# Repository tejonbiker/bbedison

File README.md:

# bbedison

The concept of the Intel Edison is great, but require skills (some skills are very advanced) to start working with this tiny invention.

The concept of  [Sparkfun Blocks](https://www.sparkfun.com/search/results?term=sparkfun+blocks) is great, but lack the access to all the pins of the Edison (else you will require several blocks).

The Arduino board is a great way to start with Intel Edison, but is to big and breaks the esscence of the edison, besides that, this board don't have access to all the pins of the Edison.

So, is necesary to build a very expensive PCB (with very small traces and very [small connector](http://www.adafruit.com/product/2227)) to do an advanced prototype of the Intel Edison? 

The response is: not, here is where the [Minibreakout](https://www.sparkfun.com/products/13025) of the Intel Edison enters to the rescue, but not alone.

The mini breakout is not [breadboard](https://cdn.sparkfun.com//assets/parts/1/0/0/1/1/13025-03.jpg) friendly, but have others adavantages:

      -Lipo management (charge and regulators)
      -Serial and OTG connections
      -Power Up sequence management

BBedison is a series of PCBs that allows you (in conjunction with Edison minibreakout ) prototype in a more friendly way.

The best of all:

      -It's cheap: BBEdison base cost 5 USD (Yes 5 USD and you are ready to plug in in your breadboard)
      -It's very easy to do it in your home

Eager to start experimenting? check it out the  BBEdison_base.

Links of interest:
Instructable of BBEdison_base:  http://www.instructables.com/id/Plug-your-Intel-Edison-in-a-breadboard/
Hackaday post:  http://hackaday.com/2015/04/01/a-stack-of-boards-for-an-edison-breadboard-adapter/

Authors:

**Federico Ramos**

tejonbiker@gmail.com

[@tejonbiker](https://twitter.com/tejonBiker)

about me ([spanish](https://tejonbiker.wordpress.com/acerca-de-mi/))

**Xhabas Jimenez**

[@Sabasacustico](https://twitter.com/Sabasacustico)

The Inventors House [Hackerspace](http://blog.theinventorhouse.org/)

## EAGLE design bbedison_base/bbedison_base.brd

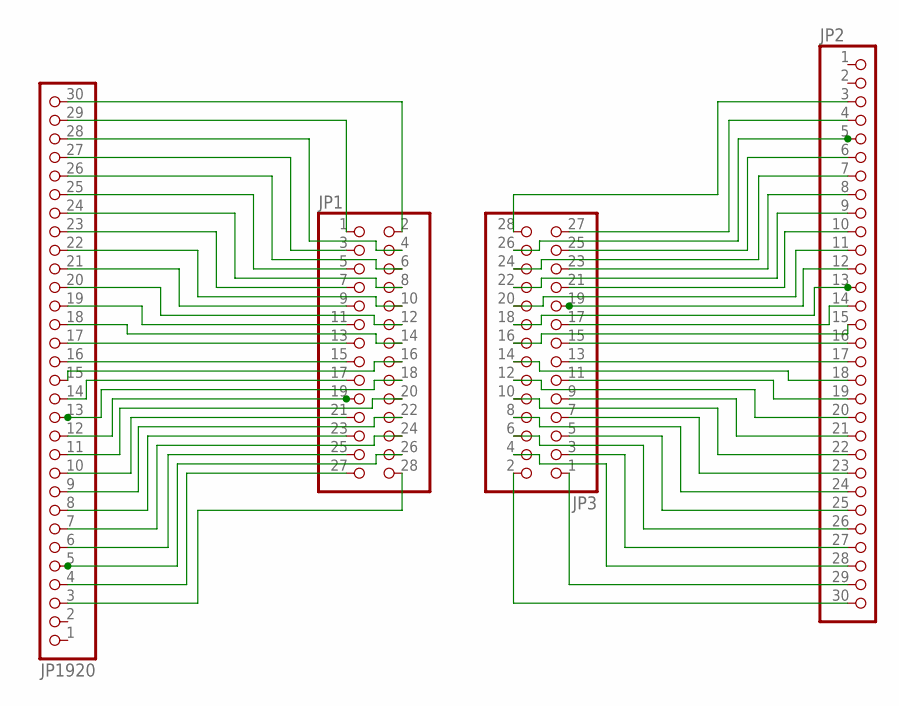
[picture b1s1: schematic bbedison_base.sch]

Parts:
JP1, JP3: PINHD-2X14; 2X14
JP2, JP1920: PINHD-1X30; 1X30

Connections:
unnamed: JP1.2, JP1920.30
unnamed: JP1.1, JP1920.29
unnamed: JP1.4, JP1920.28
unnamed: JP1.3, JP1920.27
unnamed: JP1.6, JP1920.26
unnamed: JP1.5, JP1920.25
unnamed: JP1.8, JP1920.24
unnamed: JP1.7, JP1920.23
unnamed: JP1.10, JP1920.22
unnamed: JP1.9, JP1920.21
unnamed: JP1.12, JP1920.20
unnamed: JP1.11, JP1920.19
unnamed: JP1.16, JP1920.15
unnamed: JP1.14, JP1920.18
unnamed: JP1.13, JP1920.17
unnamed: JP1.15, JP1920.16
unnamed: JP1.17, JP1920.14
unnamed: JP1.18, JP1920.13
unnamed: JP1.19, JP1920.12
unnamed: JP1.20, JP1920.11
unnamed: JP1.21, JP1920.10
unnamed: JP1.22, JP1920.9
unnamed: JP1.23, JP1920.8
unnamed: JP1.24, JP1920.7
unnamed: JP1.25, JP1920.6
unnamed: JP1.26, JP1920.5
unnamed: JP1.27, JP1920.4
unnamed: JP1.28, JP1920.3
unnamed: JP2.30, JP3.2
unnamed: JP2.29, JP3.1
unnamed: JP2.28, JP3.4
unnamed: JP2.27, JP3.3
unnamed: JP2.26, JP3.6
unnamed: JP2.25, JP3.5
unnamed: JP2.24, JP3.8
unnamed: JP2.23, JP3.7
unnamed: JP2.22, JP3.10
unnamed: JP2.21, JP3.9
unnamed: JP2.20, JP3.12
unnamed: JP2.19, JP3.11
unnamed: JP2.18, JP3.14
unnamed: JP2.17, JP3.13
unnamed: JP2.16, JP3.15
unnamed: JP2.15, JP3.16
unnamed: JP2.14, JP3.17
unnamed: JP2.13, JP3.18
unnamed: JP2.12, JP3.19
unnamed: JP2.11, JP3.20
unnamed: JP2.10, JP3.21
unnamed: JP2.9, JP3.22
unnamed: JP2.8, JP3.23
unnamed: JP2.7, JP3.24
unnamed: JP2.6, JP3.25
unnamed: JP2.5, JP3.26
unnamed: JP2.4, JP3.27
unnamed: JP2.3, JP3.28

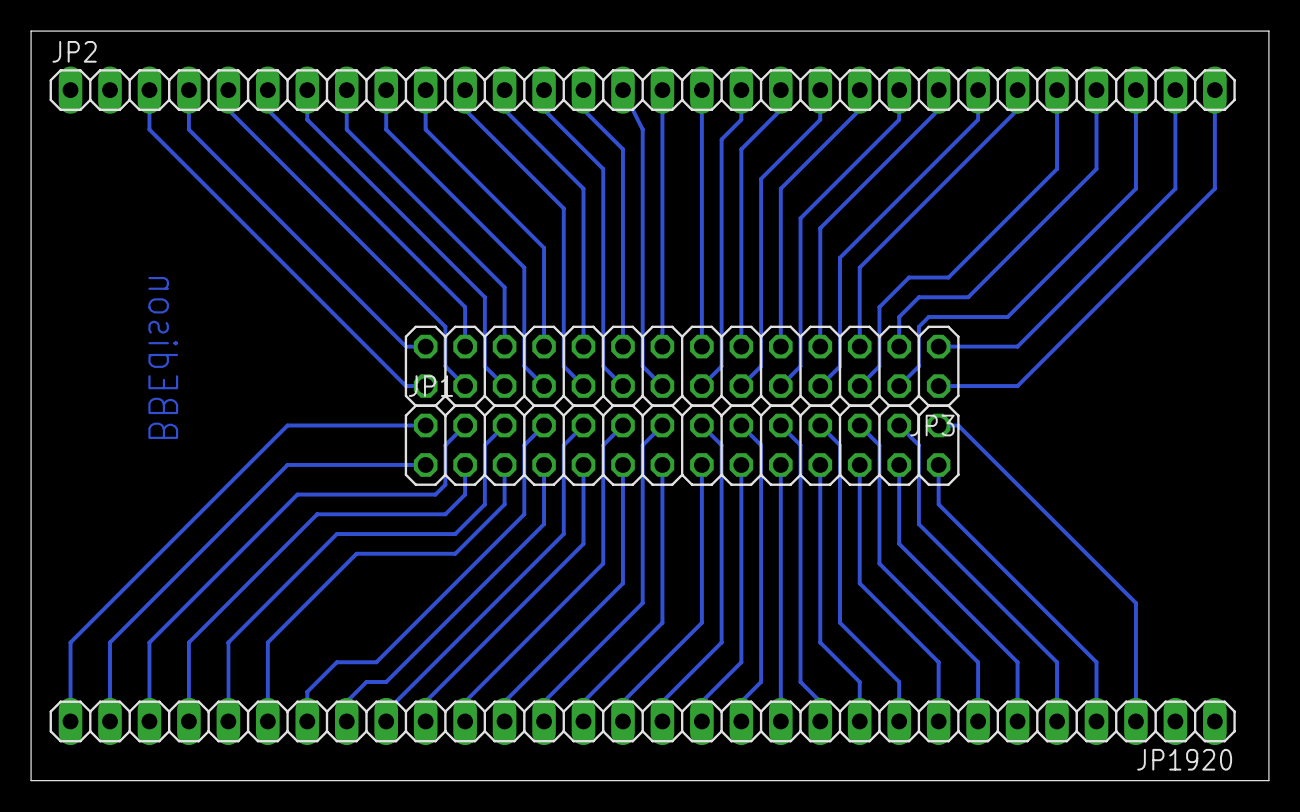
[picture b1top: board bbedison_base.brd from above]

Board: 2 copper layers, 79.7 x 48.2 mm, 4 parts (0 on the bottom side), 56 nets.

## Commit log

2015-02-08 First commit, the first verison of the breakout of minibreakout edison was added
2015-03-01 some descriptions was added
2015-03-01 Update README.md
    fixed some wronf words
2015-04-02 Update README.md
    Links added
